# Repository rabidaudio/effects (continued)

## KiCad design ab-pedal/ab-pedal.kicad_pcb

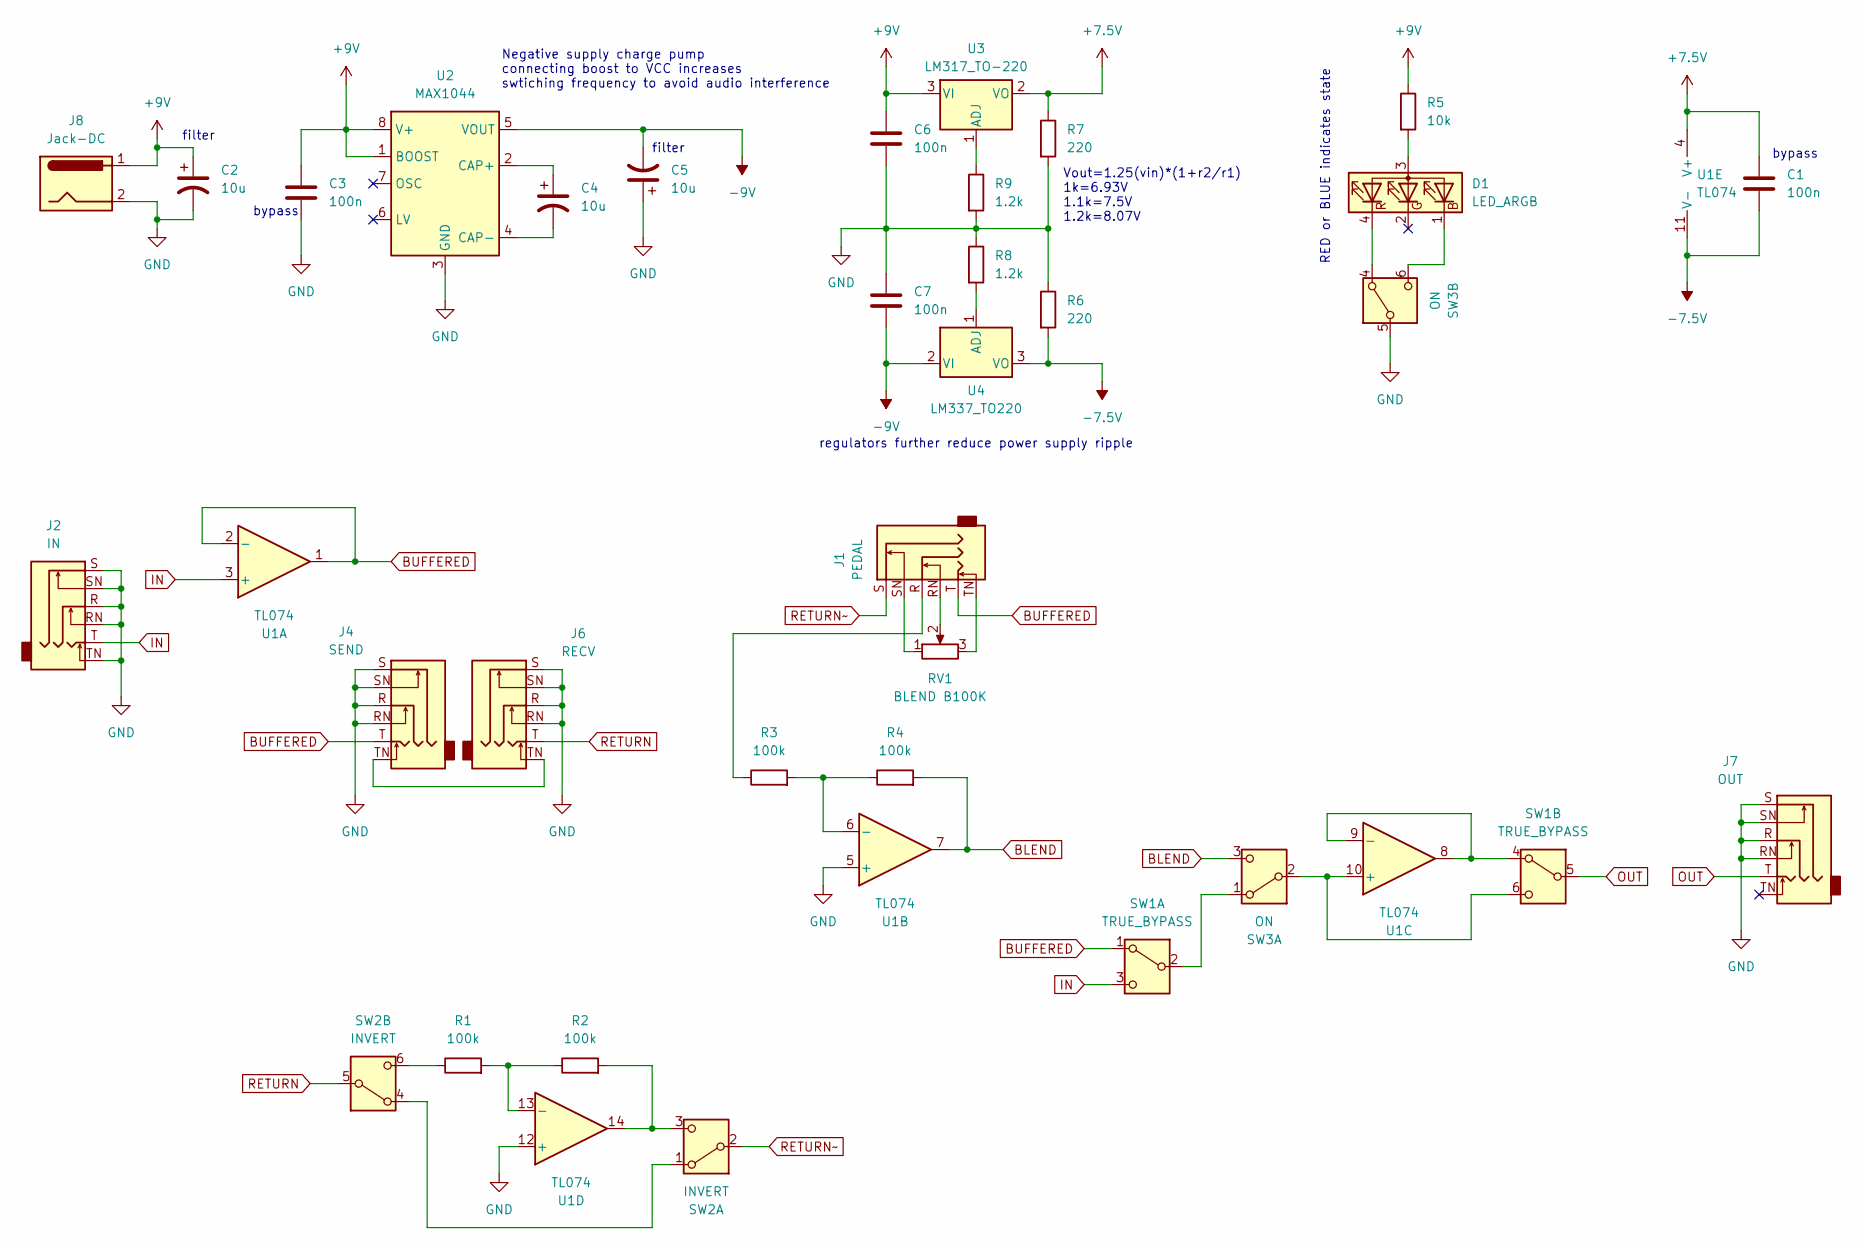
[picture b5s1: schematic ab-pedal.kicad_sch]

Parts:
C1, C3, C6, C7: 100n; C_Rect_L7.2mm_W2.5mm_P5.00mm_FKS2_FKP2_MKS2_MKP2
C2, C4, C5: 10u; CP_Radial_D4.0mm_P2.00mm
D1: LED_ARGB; LED_D5.0mm-4_RGB_Wide_Pins
J1: PEDAL; Jack_6.35mm_Neutrik_NMJ6HCD3_Horizontal
J2: IN; Jack_6.35mm_Neutrik_NMJ6HCD3_Horizontal
J4: SEND; Jack_6.35mm_Neutrik_NMJ6HCD3_Horizontal
J6: RECV; Jack_6.35mm_Neutrik_NMJ6HCD3_Horizontal
J7: OUT; Jack_6.35mm_Neutrik_NMJ6HCD3_Horizontal
J8: Jack-DC; PinHeader_1x02_P2.54mm_Vertical
R1, R2, R3, R4: 100k; R_Axial_DIN0207_L6.3mm_D2.5mm_P5.08mm_Vertical
R5: 10k; R_Axial_DIN0207_L6.3mm_D2.5mm_P5.08mm_Vertical
R6, R7: 220; R_Axial_DIN0207_L6.3mm_D2.5mm_P5.08mm_Vertical
R8, R9: 1.2k; R_Axial_DIN0207_L6.3mm_D2.5mm_P5.08mm_Vertical
RV1: BLEND B100K; Potentiometer_Alpha_RD901F-40-00D_Single_Vertical
SW1: TRUE_BYPASS; MTS-DPDT
SW2: INVERT; MTS-DPDT
SW3: ON; PinHeader_2x03_P2.54mm_Vertical
U1: TL074; DIP-14_W7.62mm
U2: MAX1044; DIP-8_W7.62mm
U3: LM317_TO-220; TO-220-3_Vertical
U4: LM337_TO220; TO-220-3_Vertical

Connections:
+7.5V: C1.1, R7.1, U1.4 (V+), U3.2 (VO)
+9V: C2.1, C3.1, C6.1, J8.1, R5.1, U2.1 (BOOST), U2.8 (V+), U3.3 (VI)
-7.5V: C1.2, R6.2, U1.11 (V-), U4.3 (VO)
-9V: C5.2, C7.2, U2.5 (VOUT), U4.2 (VI)
BLEND: R4.2, SW3.3 (C), U1.7
BUFFERED: J1.T, J4.T, SW1.1 (A), U1.1, U1.2 (-)
GND: C2.2, C3.2, C5.1, C6.2, C7.1, J2.R, J2.RN, J2.S, J2.SN, J2.TN, J4.R, J4.RN, J4.S, J4.SN, J6.R, J6.RN, J6.S, J6.SN, J7.R, J7.RN, J7.S, J7.SN, J8.2, R6.1, R7.2, R8.1, R9.2, SW3.5 (B), U1.5 (+), U1.12 (+), U2.3 (GND)
IN: J2.T, SW1.3 (C), U1.3 (+)
unnamed: D1.3 (A), R5.2
unnamed: D1.1 (BK), SW3.6 (C)
unnamed: D1.4 (RK), SW3.4 (A)
unnamed: J1.R, R3.1
unnamed: J1.RN, RV1.2
unnamed: J1.SN, RV1.1
unnamed: J1.TN, RV1.3
unnamed: J4.TN, J6.TN
unnamed: SW1.2 (B), SW3.1 (A)
unnamed: SW1.4 (A), U1.8, U1.9 (-)
unnamed: SW1.6 (C), SW3.2 (B), U1.10 (+)
unnamed: SW2.1 (A), SW2.4 (A)
unnamed: R2.2, SW2.3 (C), U1.14
unnamed: R1.1, SW2.6 (C)
unnamed: R3.2, R4.1, U1.6 (-)
unnamed: R1.2, R2.1, U1.13 (-)
unnamed: C4.1, U2.2 (CAP+)
unnamed: C4.2, U2.4 (CAP-)
unnamed: R9.1, U3.1 (ADJ)
unnamed: R8.2, U4.1 (ADJ)
OUT: J7.T, SW1.5 (B)
RETURN: J6.T, SW2.5 (B)
RETURN~: J1.S, SW2.2 (B)

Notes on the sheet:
Vout=1.25(vin)*(1+r2/r1) 1k=6.93V 1.1k=7.5V 1.2k=8.07V
Negative supply charge pump connecting boost to VCC increases swtiching frequency to avoid audio interference
bypass
filter
regulators further reduce power supply ripple
RED or BLUE indicates state

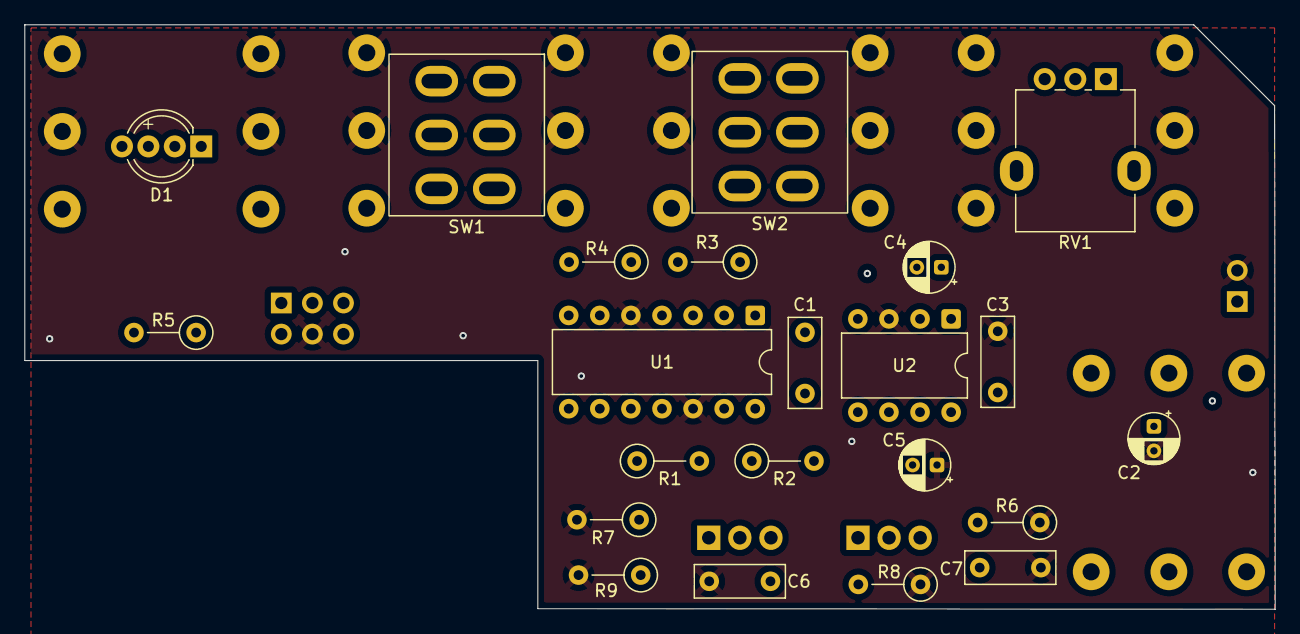
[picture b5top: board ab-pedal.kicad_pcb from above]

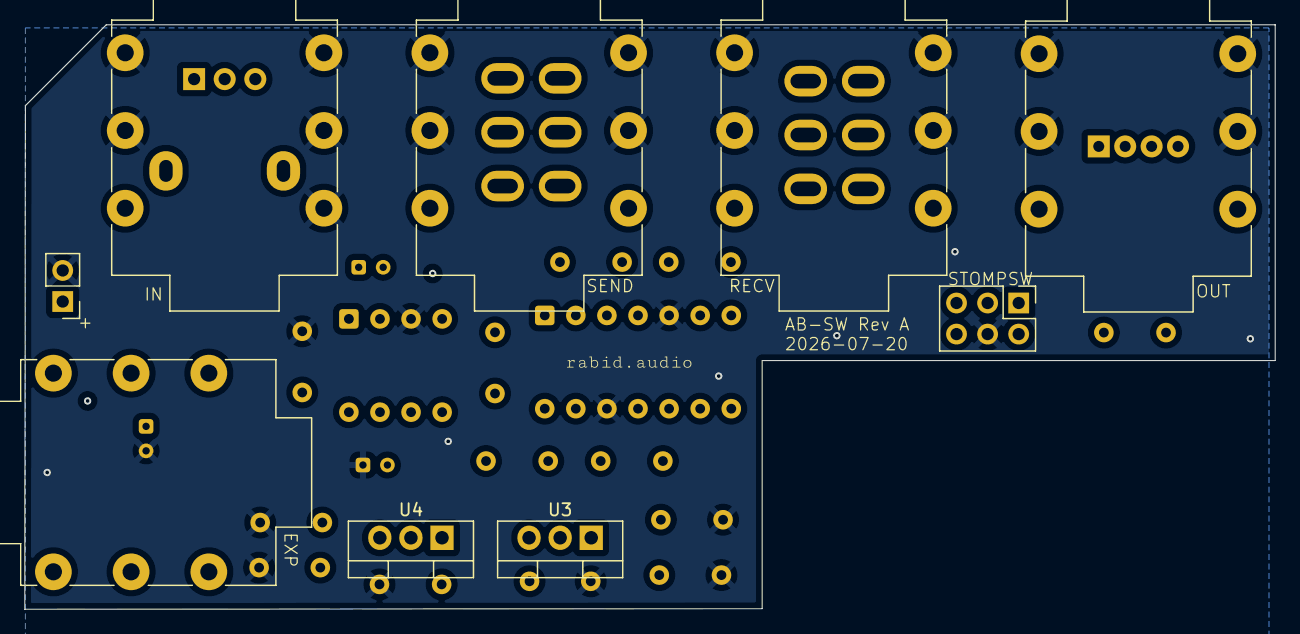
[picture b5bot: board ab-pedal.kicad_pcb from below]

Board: 4 copper layers, 102.2 x 47.8 mm, 31 parts (9 on the bottom side), 31 nets.

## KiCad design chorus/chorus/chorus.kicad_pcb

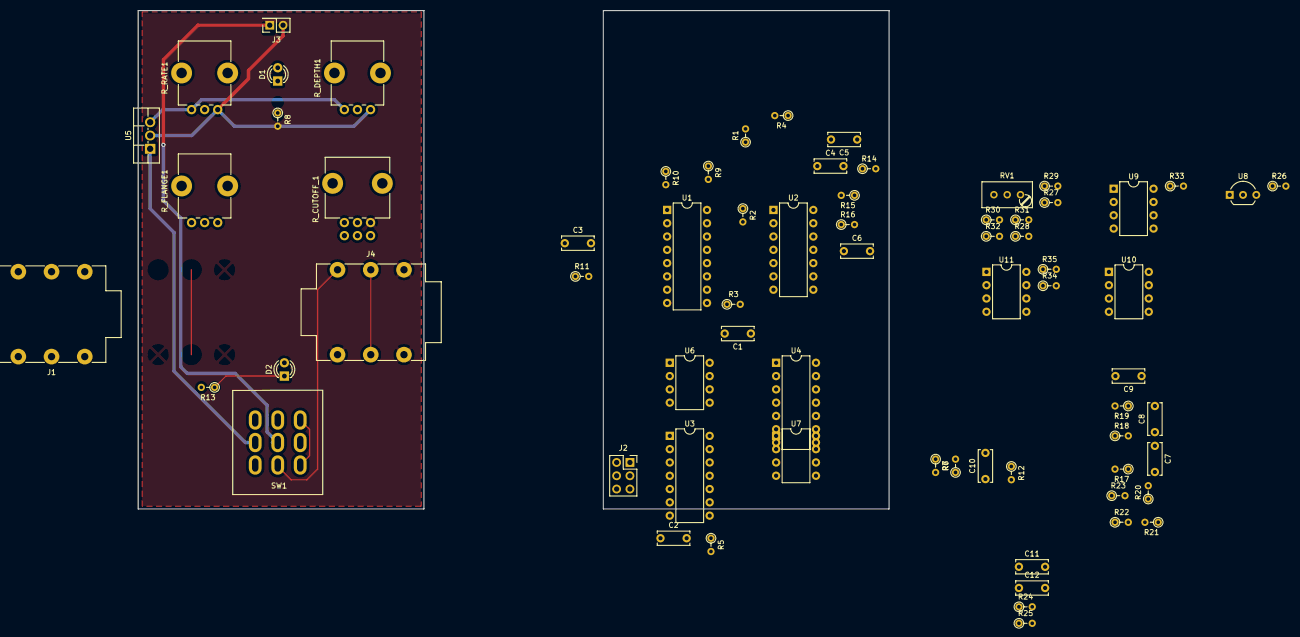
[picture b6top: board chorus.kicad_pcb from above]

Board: 2 copper layers, 70 parts (0 on the bottom side), 60 nets.

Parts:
C1: 100n; C_Disc_D6.0mm_W2.5mm_P5.00mm
C2: 220n; C_Disc_D6.0mm_W2.5mm_P5.00mm
C3: 470p; C_Disc_D6.0mm_W2.5mm_P5.00mm
C4, C7: 6.8n; C_Disc_D6.0mm_W2.5mm_P5.00mm
C5, C8: 330p; C_Disc_D6.0mm_W2.5mm_P5.00mm
C6, C9: 2.2n; C_Disc_D6.0mm_W2.5mm_P5.00mm
C10: 3.3u; C_Disc_D6.0mm_W2.5mm_P5.00mm
C11, C12: 33n; C_Disc_D6.0mm_W2.5mm_P5.00mm
D1, D2: LED; LED_D3.0mm
J1: IN; Jack_6.35mm_Neutrik_NMJ6HCD2_Horizontal
J2: ISP; PinSocket_2x03_P2.54mm_Vertical
J3: Jack-DC; PinSocket_2x01_P2.54mm_Vertical
J4: OUT; Jack_6.35mm_Neutrik_NMJ6HCD2_Horizontal
R1, R2, R3, R4, R6, R7: 1M; R_Axial_DIN0204_L3.6mm_D1.6mm_P2.54mm_Vertical
R5: 100; R_Axial_DIN0204_L3.6mm_D1.6mm_P2.54mm_Vertical
R8: 240; R_Axial_DIN0204_L3.6mm_D1.6mm_P2.54mm_Vertical
R9: 4.8k; R_Axial_DIN0204_L3.6mm_D1.6mm_P2.54mm_Vertical
R10: 2.7k; R_Axial_DIN0204_L3.6mm_D1.6mm_P2.54mm_Vertical
R11: 2.2k; R_Axial_DIN0204_L3.6mm_D1.6mm_P2.54mm_Vertical
R12, R24, R25, R27: 1K; R_Axial_DIN0204_L3.6mm_D1.6mm_P2.54mm_Vertical
R13: 220; R_Axial_DIN0204_L3.6mm_D1.6mm_P2.54mm_Vertical
R14, R17: 11k; R_Axial_DIN0204_L3.6mm_D1.6mm_P2.54mm_Vertical
R15: 150k; R_Axial_DIN0204_L3.6mm_D1.6mm_P2.54mm_Vertical
R16: 47k; R_Axial_DIN0204_L3.6mm_D1.6mm_P2.54mm_Vertical
R18: 75K; R_Axial_DIN0204_L3.6mm_D1.6mm_P2.54mm_Vertical
R19: 51K; R_Axial_DIN0204_L3.6mm_D1.6mm_P2.54mm_Vertical
R20, R21, R29, R30, R31, R32: 100K; R_Axial_DIN0204_L3.6mm_D1.6mm_P2.54mm_Vertical
R22, R23: 5.6K; R_Axial_DIN0204_L3.6mm_D1.6mm_P2.54mm_Vertical
R26: 500K; R_Axial_DIN0204_L3.6mm_D1.6mm_P2.54mm_Vertical
R28: 5.6k; R_Axial_DIN0204_L3.6mm_D1.6mm_P2.54mm_Vertical
R33: 330; R_Axial_DIN0204_L3.6mm_D1.6mm_P2.54mm_Vertical
R34: 91K; R_Axial_DIN0204_L3.6mm_D1.6mm_P2.54mm_Vertical
R35: 30K; R_Axial_DIN0204_L3.6mm_D1.6mm_P2.54mm_Vertical
RV1: R_TRIM_10K; Potentiometer_Trimmer_Bourns_3296W
R_CUTOFF_1: 100K; Potentiometer_Alps_RK09L_Double_Vertical
R_DEPTH1: 100K; Potentiometer_Alps_RK09K_Single_Vertical
R_FLANGE1: 1M; Potentiometer_Alps_RK09K_Single_Vertical
R_RATE1: 100K; Potentiometer_Alps_RK09K_Single_Vertical
SW1: SW_3PDT_x3; Stompbox Switch
U1: LM13700; DIP-16_W7.62mm
U2, U3, U4: TL074; DIP-14_W7.62mm
U5: LM7805; TO-220F-3_Vertical
U6, U11: TL072; DIP-8_W7.62mm
U7: MN3207; DIP-8_W7.62mm
U8: TLE2426xLP; TO-92_Inline_Wide
U9: ATTINY85-20PU; DIP-8_W7.62mm
U10: MN3102; DIP-8_W7.62mm

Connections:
+5V: D2.2 (A), J2.2 (VCC), R10.1, R_DEPTH1.3, R_RATE1.3, U5.3 (VO), U7.5 (VDD), U9.8 (VCC), U10.3 (VDD)
+9V: SW1.4, U2.4 (V+), U5.1 (VI), U6.8 (V+), U8.3 (IN)
/Anti-Aliasing Filter/IN: R14.2, R29.2, U3.6 (-), U3.7
/Anti-Aliasing Filter/OUT: U6.1, U6.2 (-), U7.3 (IN)
/Clock Generator/CLOCK: R12.1, R33.2, U10.7 (OX1)
/Reconstruction Filter/IN: R22.1, R23.1, R34.2
/Reconstruction Filter/OUT: R4.2, U6.6 (-), U6.7
/Tone Filter/DRY_OUT: R6.2, R32.1, U4.7
/Tone Filter/IN: C11.2, R2.1, R30.2, U2.1
GND: C2.1, C10.1, J2.6 (GND), J3.2, R8.2, R12.2, R13.2, R_DEPTH1.1, R_RATE1.1, U2.11 (V-), U5.2 (GND), U6.4 (V-), U7.1 (GND), U8.2 (COMMON), U9.4 (GND), U10.1 (GND)
GNDA: C3.2, C4.1, C5.1, C7.1, C8.1, J1.S, J1.SN, J1.TN, J4.S, J4.SN, J4.TN, R11.2, R20.1, R21.1, R31.1, R_CUTOFF_1.1, U1.4 (-), U2.3 (+), U3.3 (+), U8.1 (OUT)
MISO: J2.1 (MISO), U9.6 (PB1)
MOSI: D1.2 (A), J2.4 (MOSI), R5.2, U9.5 (PB0)
unnamed: C1.1, SW1.7
unnamed: C1.2, R28.2, RV1.2, RV1.3
unnamed: R5.1, R9.1
unnamed: C3.1, U1.5, U1.13 (-)
unnamed: C4.2, R14.1, R15.2
unnamed: C5.2, R16.1, U6.3 (+)
unnamed: C6.2, R15.1, R16.2
unnamed: C7.2, R17.1, R18.2
unnamed: C8.2, R19.1, U6.5 (+)
unnamed: C9.2, R18.1, R19.2
unnamed: C10.2, U7.4 (VGG), U10.8 (VGG_OUT)
unnamed: C11.1, C12.2, R25.2
unnamed: C12.1, R24.2, U2.5 (+)
unnamed: R28.1, U3.5 (+)
unnamed: R35.1, U11.5 (+)
unnamed: R17.2, U11.6 (-), U11.7
unnamed: R34.1, R35.2
unnamed: D1.1 (K), R8.1
unnamed: D2.1 (K), R13.1
unnamed: J1.R, J1.RN, J4.R, J4.RN
unnamed: J1.T, SW1.2
unnamed: J3.1, SW1.5
unnamed: J4.T, SW1.8
unnamed: R1.1, R2.2, R_FLANGE1.3, U2.2 (-)
unnamed: R1.2, R7.2, SW1.1
unnamed: R3.1, R_FLANGE1.1, R_FLANGE1.2
unnamed: R9.2, U1.1
unnamed: R10.2, U1.16
unnamed: R11.1, U1.3 (+), U1.7, U1.12, U1.14 (+)
unnamed: R20.2, R23.2, U7.8 (OUT2)
unnamed: R21.2, R22.2, U7.7 (OUT1)
unnamed: R24.1, R_CUTOFF_1.2, R_CUTOFF_1.3
unnamed: R25.1, R_CUTOFF_1.5, R_CUTOFF_1.6
unnamed: R3.2, R26.1, U3.1
unnamed: R4.1, R6.1, R7.1, R26.2, U3.2 (-)
unnamed: R27.1, RV1.1
unnamed: R27.2, R_CUTOFF_1.4, U2.6 (-), U2.7
unnamed: R29.1, R32.2, U4.6 (-)
unnamed: R30.1, R31.2, U4.5 (+)
unnamed: R33.1, U1.8
unnamed: R_DEPTH1.2, U9.3 (PB4)
unnamed: R_RATE1.2, U9.2 (PB3)
unnamed: SW1.3, SW1.9
unnamed: U7.2 (CP1), U10.2 (CP1)
unnamed: U7.6 (CP2), U10.4 (CP2)
SCK: J2.3 (SCK), U9.7 (PB2)
~RST: J2.5 (~RST), U9.1 (PB5)

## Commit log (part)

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2022-04-24 work so far on chorus
2022-04-25 working digital clock
2022-05-01 controllable lfo
2022-05-01 worked out timer0 behavior
2022-05-02 working timer
2022-05-06 calculated filters, updated parts
2022-05-08 learnings from breadboard, attiny resolution is too low
2022-05-15 redesign
2022-06-11 unsaved changes
2022-06-11 improve lfo resolution, rework depth and mix config
2022-06-11 add wet/dry mix and recalculate filters
2022-06-16 update filters
2022-06-16 remove dry/wet, add higher dry frequencies
2022-06-18 improve BP calculations imperically
2022-06-18 assembled psu and clock
2022-07-17 create splitter circuit
2022-07-18 do pcb
2022-07-18 rework switches to allow low/high/all send and bypass
2022-07-20 fix some bugs
2022-07-24 create decal
2022-07-26 bug fixes
2022-08-04 cleanup
2022-08-27 rev b based on learnings from assembly
2022-09-03 rev B
2023-01-01 layout for digital effects system
2023-02-04 update to kicad 6
2023-02-05 add output buffer
2023-02-20 solid progress. working effects and knobs, plan for circuit
2023-03-12 proved out all the components
2023-03-17 proved out assembly
2023-08-05 refactor
2023-08-05 switch b board
2023-08-05 create gerbers
2023-08-05 generate bom
2023-08-10 more adjustments
2023-08-30 rev D
2023-08-31 mechanicals and measurements
2023-09-02 fix some spacing, start on graphics
2023-09-03 working on script to generate locations
2023-09-04 rework graphics and finalize case
2023-09-04 updated generated outputs and docs
2023-09-29 update assembly instructions
2023-09-29 rev e
2023-11-09 update capacitor footprints
2023-11-09 switch to IPC cables for switch
2023-11-11 swap wet-dry direction to be more intuitive
2024-09-11 uncommited changes
2024-09-12 redesign using VCF
2024-09-13 initial layout pass
2024-09-14 do layout
2024-09-14 mvoe
2024-09-15 fix pot orientation
2024-09-16 re-design mixer
2024-09-16 re-layout
2024-09-16 new ribbon cable
2024-09-16 re-annotate
2024-09-16 more filter caps
2024-09-16 layout fixes
2025-04-04 update input buffer
2025-04-04 redesign board: rev F
2026-01-12 working logic
